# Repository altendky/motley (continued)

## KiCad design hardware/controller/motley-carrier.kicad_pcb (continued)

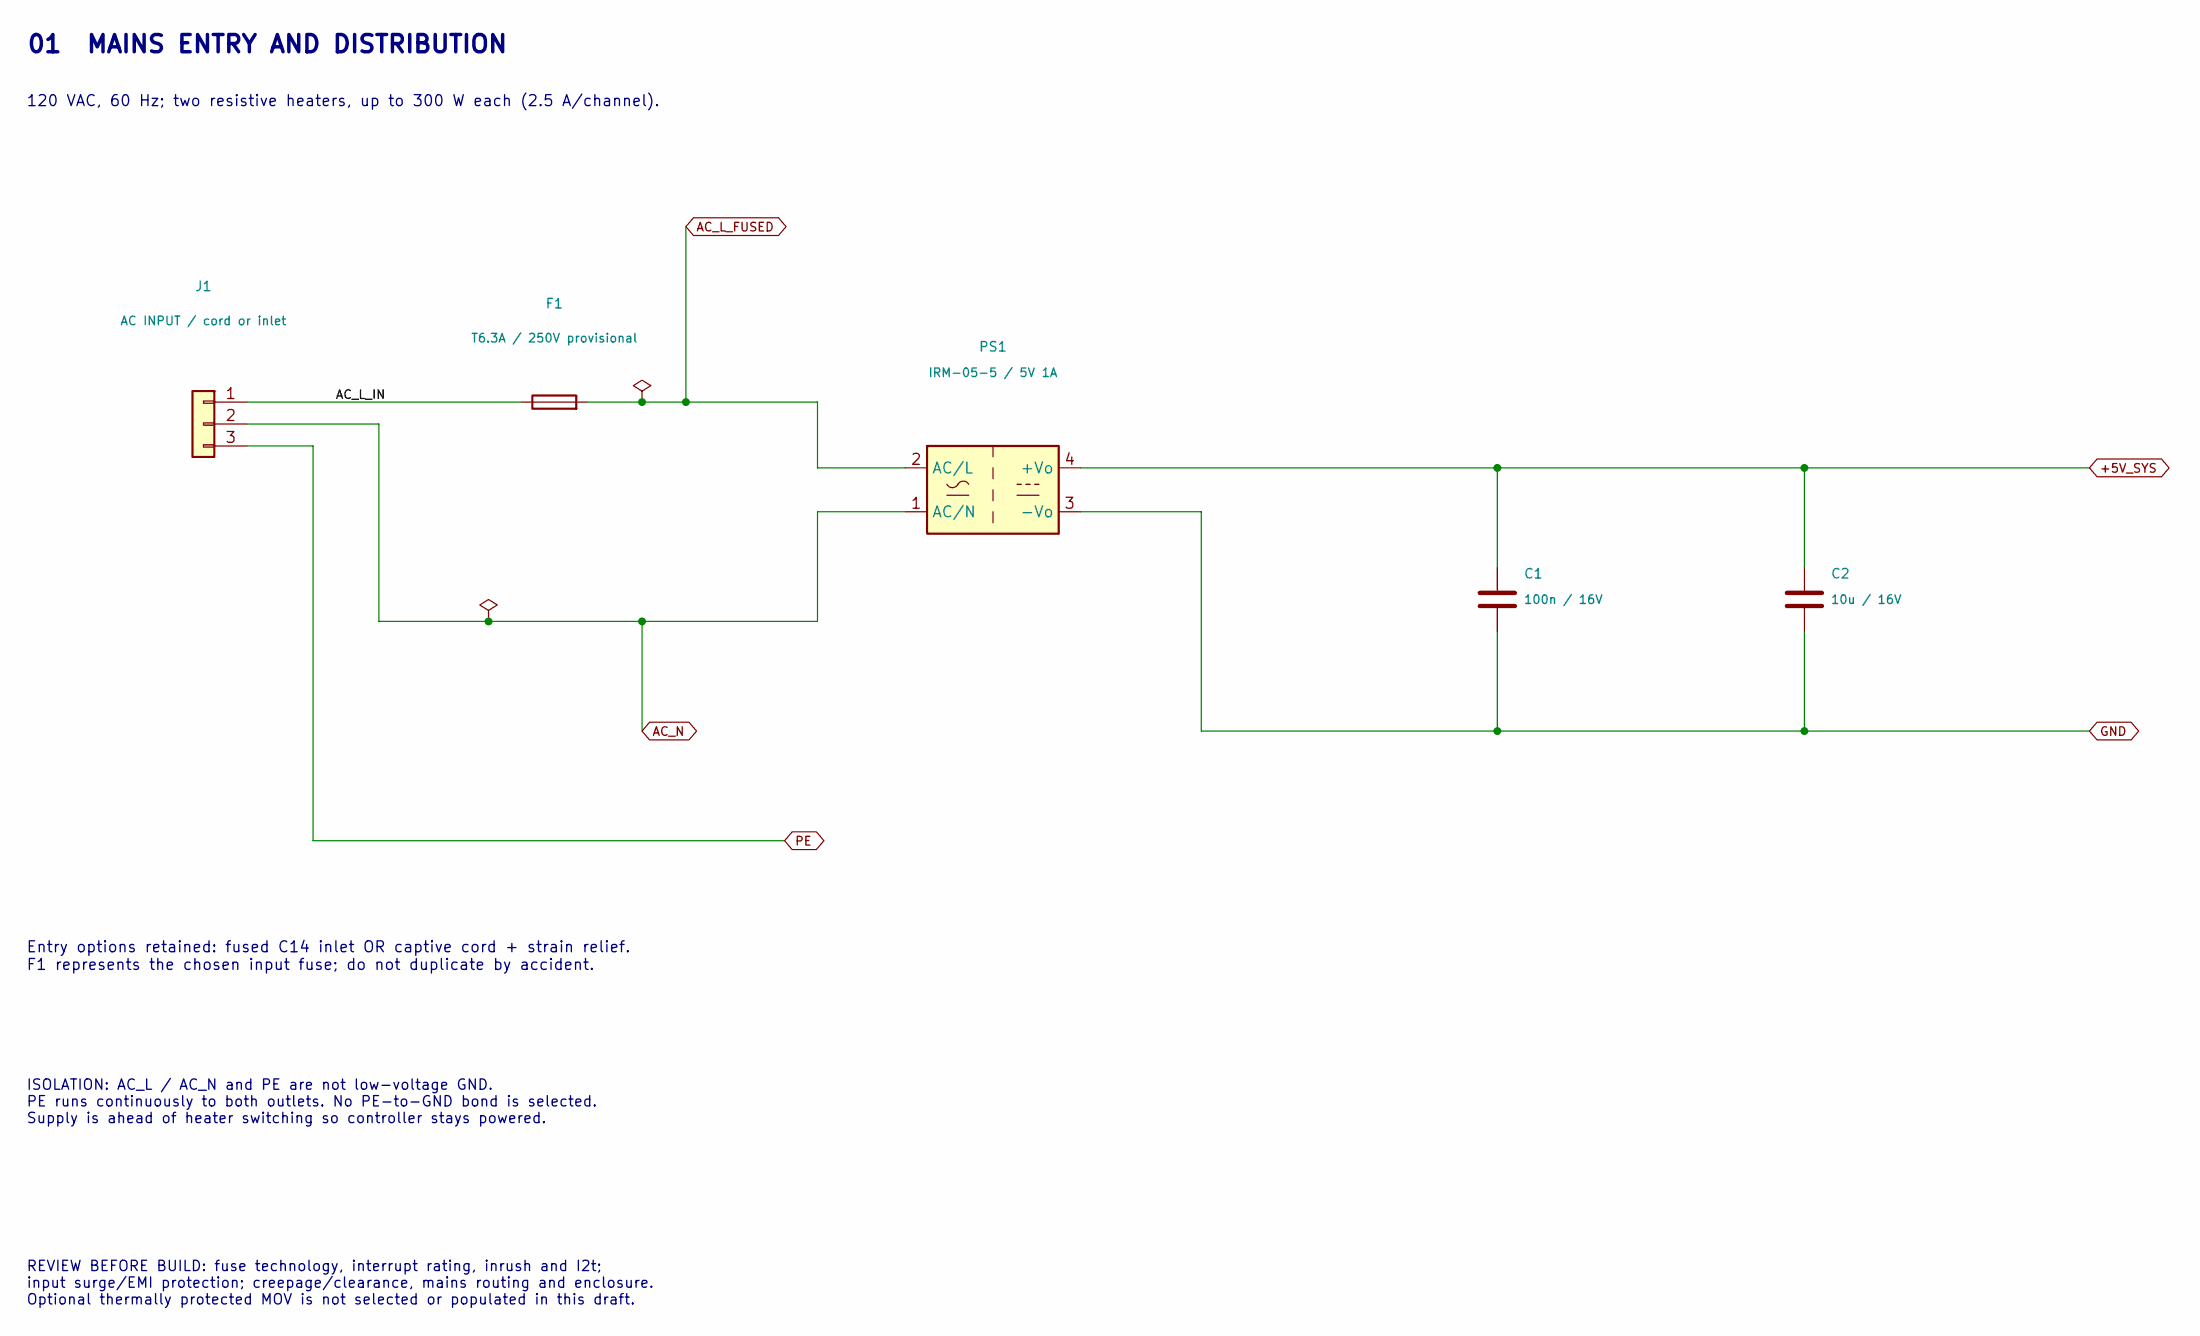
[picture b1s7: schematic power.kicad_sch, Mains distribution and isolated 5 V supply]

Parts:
C1: 100n / 16V; C_0805_2012Metric
C2: 10u / 16V; C_0805_2012Metric
F1: T6.3A / 250V provisional; Fuseholder_Schurter_OGN_0031.8201_P22.50mm_Covered; MPN 0031.8201; LCSC C3204125
J1: AC INPUT / cord or inlet; TerminalBlock_GOOSVN_GS007S_P5.08mm_1x03_Horizontal; MPN GS007S-5.08-03P-11-00A(H); LCSC C5142603
PS1: IRM-05-5 / 5V 1A; Converter_ACDC_MeanWell_IRM-05-xx_THT; LCSC C48603696

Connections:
+5V_SYS: C1.1, C2.1, PS1.4 (+Vo); also elsewhere on the board
/Mains input and isolated 5 V supply/AC_L_IN: F1.1, J1.1
AC_L_FUSED: F1.2, PS1.2 (AC/L); also elsewhere on the board
AC_N: J1.2, PS1.1 (AC/N); also elsewhere on the board
GND: C1.2, C2.2, PS1.3 (-Vo); also elsewhere on the board
PE: J1.3; also elsewhere on the board

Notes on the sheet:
01 MAINS ENTRY AND DISTRIBUTION
120 VAC, 60 Hz; two resistive heaters, up to 300 W each (2.5 A/channel).
ISOLATION: AC_L / AC_N and PE are not low-voltage GND. PE runs continuously to both outlets. No PE-to-GND bond is selected. Supply is ahead of heater switching so controller stays powered.
Entry options retained: fused C14 inlet OR captive cord + strain relief. F1 represents the chosen input fuse; do not duplicate by accident.
REVIEW BEFORE BUILD: fuse technology, interrupt rating, inrush and I2t; input surge/EMI protection; creepage/clearance, mains routing and enclosure. Optional thermally protected MOV is not selected or populated in this draft.

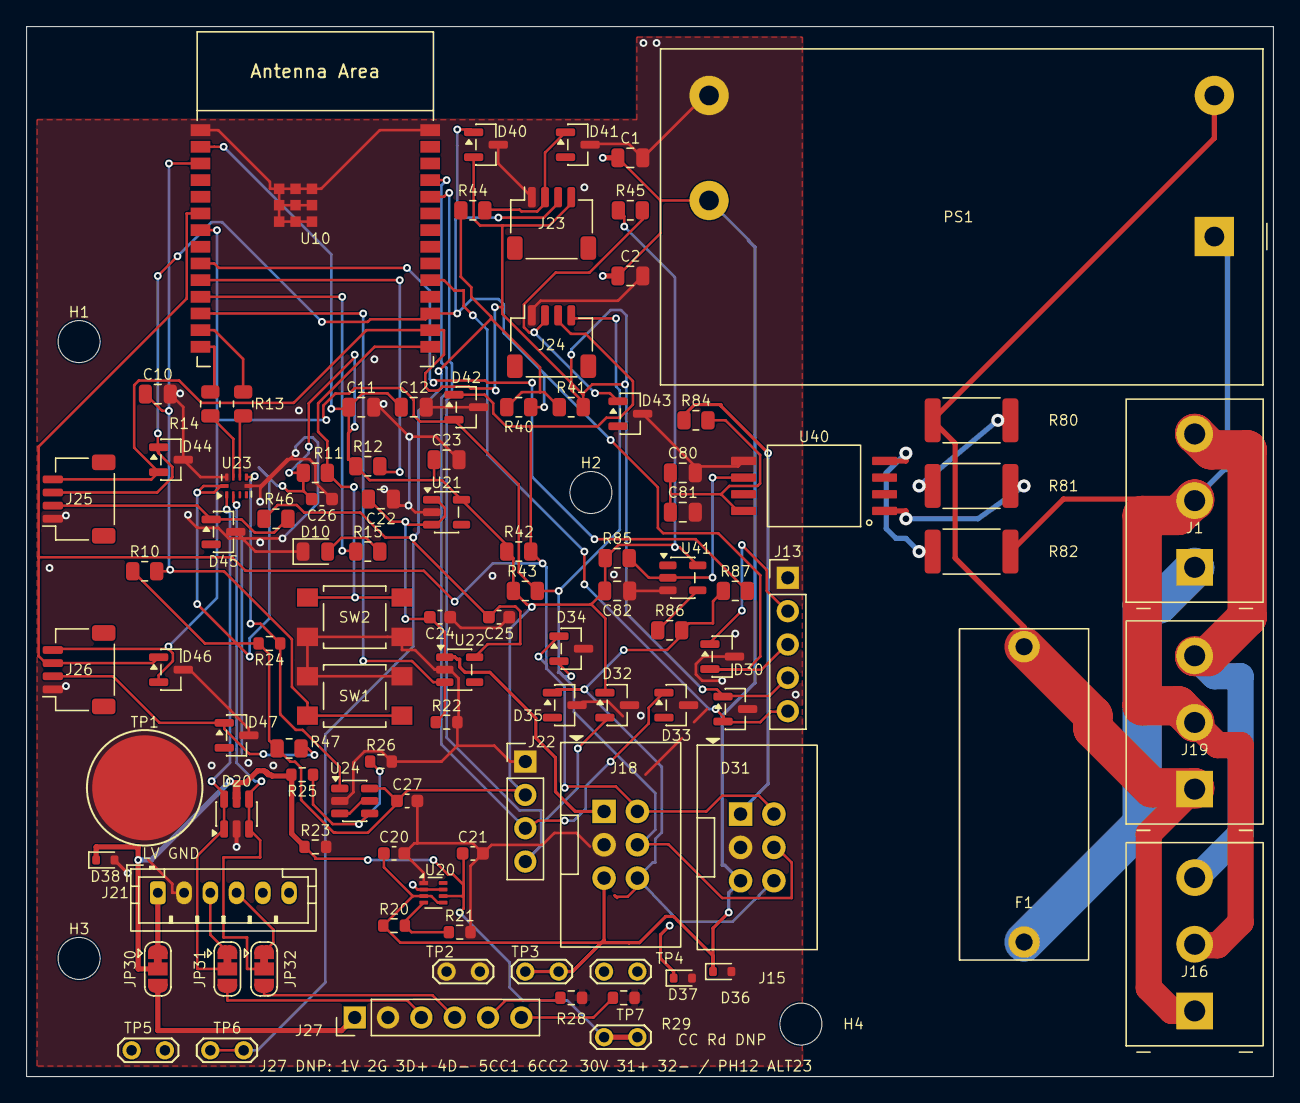
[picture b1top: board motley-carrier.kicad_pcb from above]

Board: 4 copper layers, 95.0 x 80.0 mm, 104 parts (0 on the bottom side), 53 nets.

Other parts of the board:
H1, H2, H3, H4: M3 / PROVISIONAL; MountingHole_3.2mm_M3

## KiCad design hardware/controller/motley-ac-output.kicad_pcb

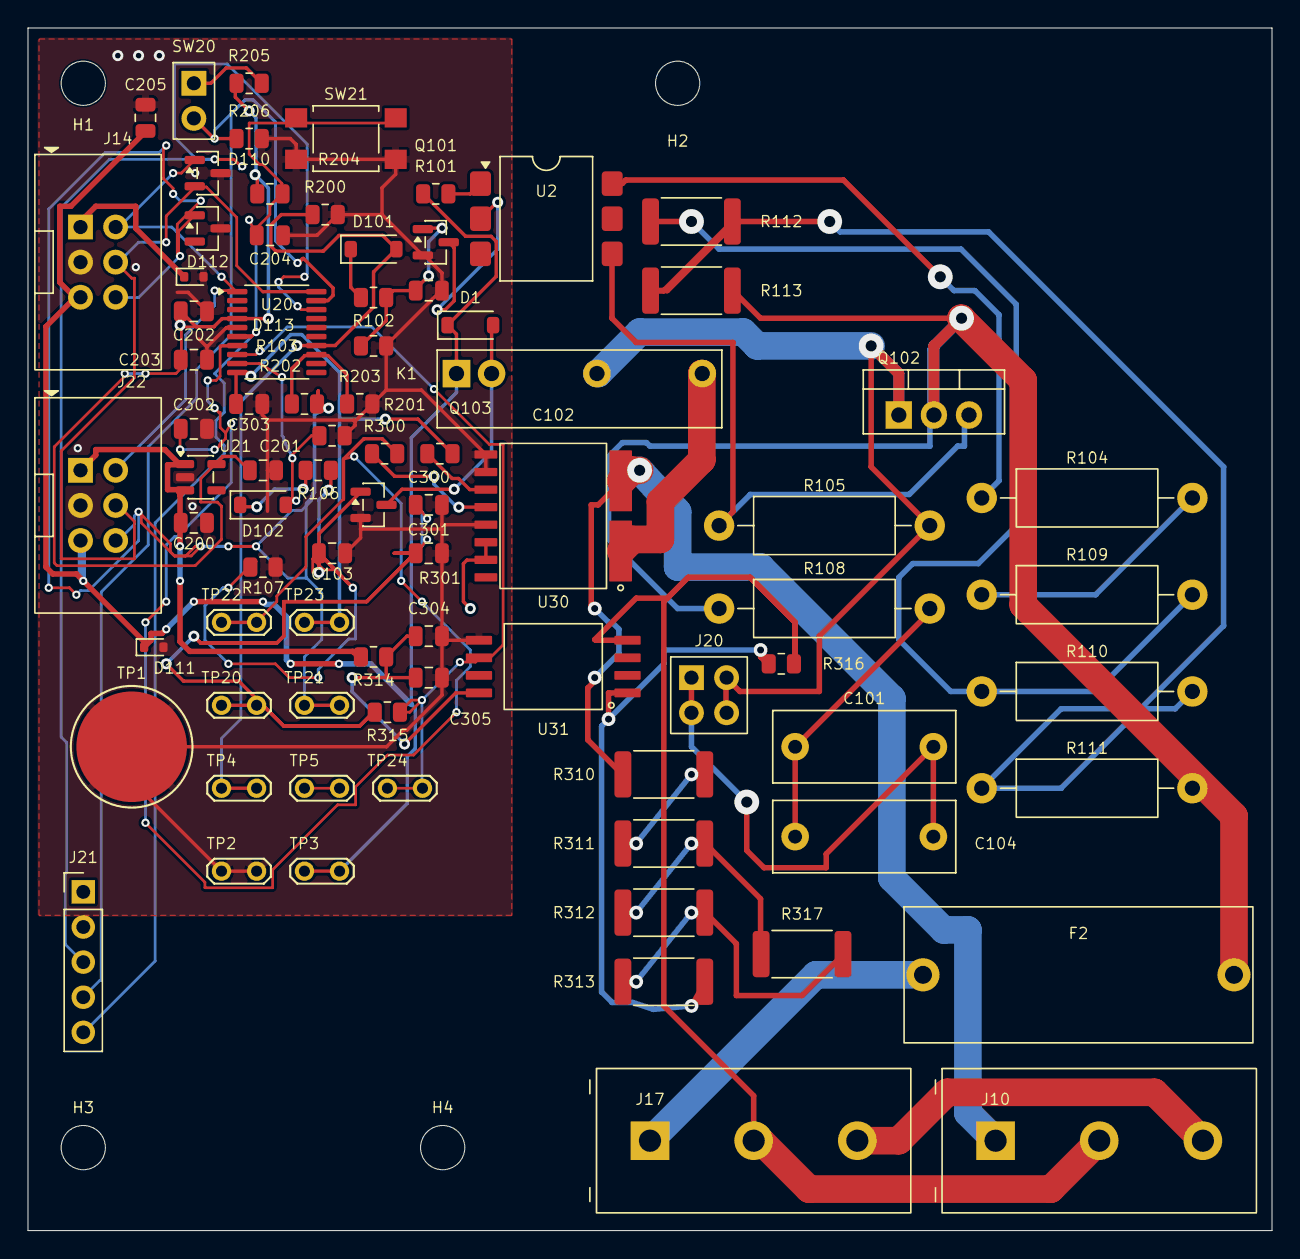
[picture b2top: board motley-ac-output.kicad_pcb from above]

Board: 4 copper layers, 90.0 x 87.0 mm, 85 parts (0 on the bottom side), 45 nets.

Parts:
C101, C104: 4n7 / pulse; C_Rect_L13.0mm_W5.0mm_P10.00mm_FKS3_FKP3_MKS4
C102: 1n / 50V; C_0805_2012Metric
C103: 100n / 50V; C_0805_2012Metric
C200: 1u / 16V; C_0805_2012Metric
C201: 4.7u / 10V; C_0805_2012Metric
C202, C204, C205, C304: 100n / 16V; C_0805_2012Metric
C203, C301: 1u / 10V; C_0805_2012Metric
C300: 100n / 10V; C_0805_2012Metric
C302, C303: 1n / 10V; C_0805_2012Metric
C305: 10n / 16V; C_0805_2012Metric
D1, D101, D102: 1N4148W; D_SOD-123
D110, D112: PESD5V0S2BT,215; SOT-23
D111, D113: ESD5Z6.0T1G; D_SOD-523
F2: T3.15A provisional; Fuseholder_Schurter_OGN_0031.8201_P22.50mm_Covered
H1, H2, H3, H4: M3 / PROVISIONAL; MountingHole_3.2mm_M3
J10: Qualtek 738W-X2/03 (wired); TerminalBlock_GOOSVN_GS007S_P7.50mm_1x03_Horizontal
J14: OUTPUT BUS / IDC6; Kinghelm_KH-2.54PH180-2X3P-L8.9_Vertical
J17: MAINS LINK / provisional terminal; TerminalBlock_GOOSVN_GS007S_P7.50mm_1x03_Horizontal
J20: SNUBBER CONFIG; Samtec_HMTSW-102-07-L-D-200_Vertical
J21: 3V3 SWD / SERVICE; PinHeader_1x05_P2.54mm_Vertical
J22: OUTPUT BUS / DNP; Kinghelm_KH-2.54PH180-2X3P-L8.9_Vertical
K1: G6DN-1A-L DC5; Relay_G6DN_1A_L_DC5_Study
Q101, Q103: MMBT3904; SOT-23
Q102: BTA08-600SWRG; TO-220-3_Vertical
R101: 270; R_0805_2012Metric
R102: 470; R_0805_2012Metric
R103, R107, R204: 10k; R_0805_2012Metric
R104, R109, R110, R111: 1k2 / PR02; Vishay_PR02_P15.24mm
R105, R108: 330 / PR02; Vishay_PR02_P15.24mm
R106: 200 / 1%; R_0805_2012Metric
R112, R113: 0 / LOW bypass; R_2512_6332Metric
R200, R201: 100k / OFF; R_0805_2012Metric
R202: 1k / SYNC; R_0805_2012Metric
R203: 100k / SYNC default; R_0805_2012Metric
R205: 1k / boot bias; R_0805_2012Metric
R206: 47k / RUN; R_0805_2012Metric
R300, R301: 100; R_0805_2012Metric
R310, R311, R312, R317: 8k2; R_2512_6332Metric
R313: 0 / LOW link; R_2512_6332Metric
R314: 240; R_0805_2012Metric
R315: 4k7; R_0805_2012Metric
R316: 2k7; R_0805_2012Metric
SW20: RUN open / RECOVERY closed; Samtec_HMTSW-102-07-G-S-200_Vertical
SW21: RESET; SW_SPST_TL3305A
TP1: TOUCH LV GND; TouchGround_8mm
TP2: GND / LOOP; WireLoop_P2.54
TP3: +5V_SYS / LOOP; WireLoop_P2.54
TP4: HEAT_EN / LOOP; WireLoop_P2.54
TP5: CUT_EN / LOOP; WireLoop_P2.54
TP20: +3V3_OUT; WireLoop_P2.54
TP21: LINE_SYNC; WireLoop_P2.54
TP22: CURRENT_V; WireLoop_P2.54
TP23: CURRENT_REF; WireLoop_P2.54
TP24: OUT_VOLT_N; WireLoop_P2.54
U2: VO3053-X007T / RANDOM PHASE; VO3053_Option7_Study
U20: STM32C011F6P6 / C5456198; TSSOP-20_4.4x6.5mm_P0.65mm
U21: AP2112K-3.3TRG1 / LOGIC; SOT-23-5
U30: TMCS1123B5AQDVGR; TMCS1123_DVG10_Study
U31: ACPL-K370-500E; ACPL_K37x_SSO8_Study

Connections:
+3V3_OUT: C201.1, C202.1, C203.1, C300.1, C301.1, J21.1, R204.1, R205.1, R315.1, TP20.1, U20.4, U21.5, U30.8, U30.9
+5V_LOGIC: C200.1, D113.1, J14.1, J22.1, R314.1, U21.1, U21.3
+5V_SYS: C205.1, D1.1 (K), D111.1, J14.5, J22.5, K1.1 (COIL), R101.1, TP3.1
/Heater 1/TRIAC_A1: J20.2, J20.4, K1.5 (NO), Q102.1 (A1), R105.2
/Local output MCU, power and recovery/OUT_BOOT0_SWCLK: J21.4, R206.1, SW20.2, U20.19
/Local output MCU, power and recovery/OUT_NRST: C204.1, J21.5, R204.2, SW21.1, U20.6
/Local output MCU, power and recovery/OUT_SWDIO: J21.3, U20.18
/Local output MCU, power and recovery/SYNC_IN: R202.1, R203.1, U20.13
AC_L_FUSED: F2.1, J17.1
AC_N: J10.2, J17.2, R316.2, U31.4
CURRENT_REF: C303.1, R301.2, TP23.1, U20.10
CURRENT_V: C302.1, R300.2, TP22.1, U20.7
CUT_EN: D102.2, R201.1, TP5.1, U20.9
CUT_L_UNSENSED: K1.8 (COM), U30.1
GND: C102.2, C103.2, C200.2, C201.2, C202.2, C203.2, C204.2, C205.2, C300.2, C301.2, C302.2, C303.2, C304.2, C305.2, D110.3, D111.2, D112.3, D113.2, J14.3, J21.2, J22.3, Q101.2 (E), Q103.2 (E), R103.2, R107.2, R200.2, R201.2, R203.2, R206.2, SW21.2, TP1.1, TP2.1, U20.5, U21.2, U30.3, U30.4, U30.7, U31.5
HEAT_EN: D101.2, R200.1, TP4.1, U20.14
LINE_SYNC: D112.1, J14.6, J22.6, R202.2, TP21.1
unnamed: C101.1, C104.1, R108.2
unnamed: D1.2 (A), K1.2 (COIL), Q103.3 (C)
unnamed: D101.1, R102.1
unnamed: D102.1, R106.1
unnamed: C101.2, C104.2, J20.1, J20.3
unnamed: C102.1, Q101.1 (B), R102.2, R103.1
unnamed: Q101.3 (C), U2.2
unnamed: F2.2, Q102.2 (A2), R108.1, R111.2, R113.2
unnamed: Q102.3 (G), R105.1, U2.4
unnamed: C103.1, Q103.1 (B), R106.2, R107.1
unnamed: R101.2, U2.1
unnamed: R104.1, U2.6
unnamed: R104.2, R109.1
unnamed: R109.2, R110.1, R112.1
unnamed: R110.2, R111.1, R112.2, R113.1
unnamed: R310.2, R311.1
unnamed: R311.2, R312.1, R317.1
unnamed: R312.2, R313.1, R317.2
unnamed: R205.2, SW20.1
unnamed: R300.1, U30.6
unnamed: R301.1, U30.5
unnamed: R313.2, R316.1, U31.1
unnamed: C304.1, C305.1, R314.2, U31.8
OUTLET_L: J10.1, R310.1, U30.2
OUT_SCL: D110.2, J14.4, J22.4, U20.20
OUT_SDA: D110.1, J14.2, J22.2, U20.1
OUT_VOLT_N: R315.2, TP24.1, U20.8, U31.6
PE: J10.3, J17.3

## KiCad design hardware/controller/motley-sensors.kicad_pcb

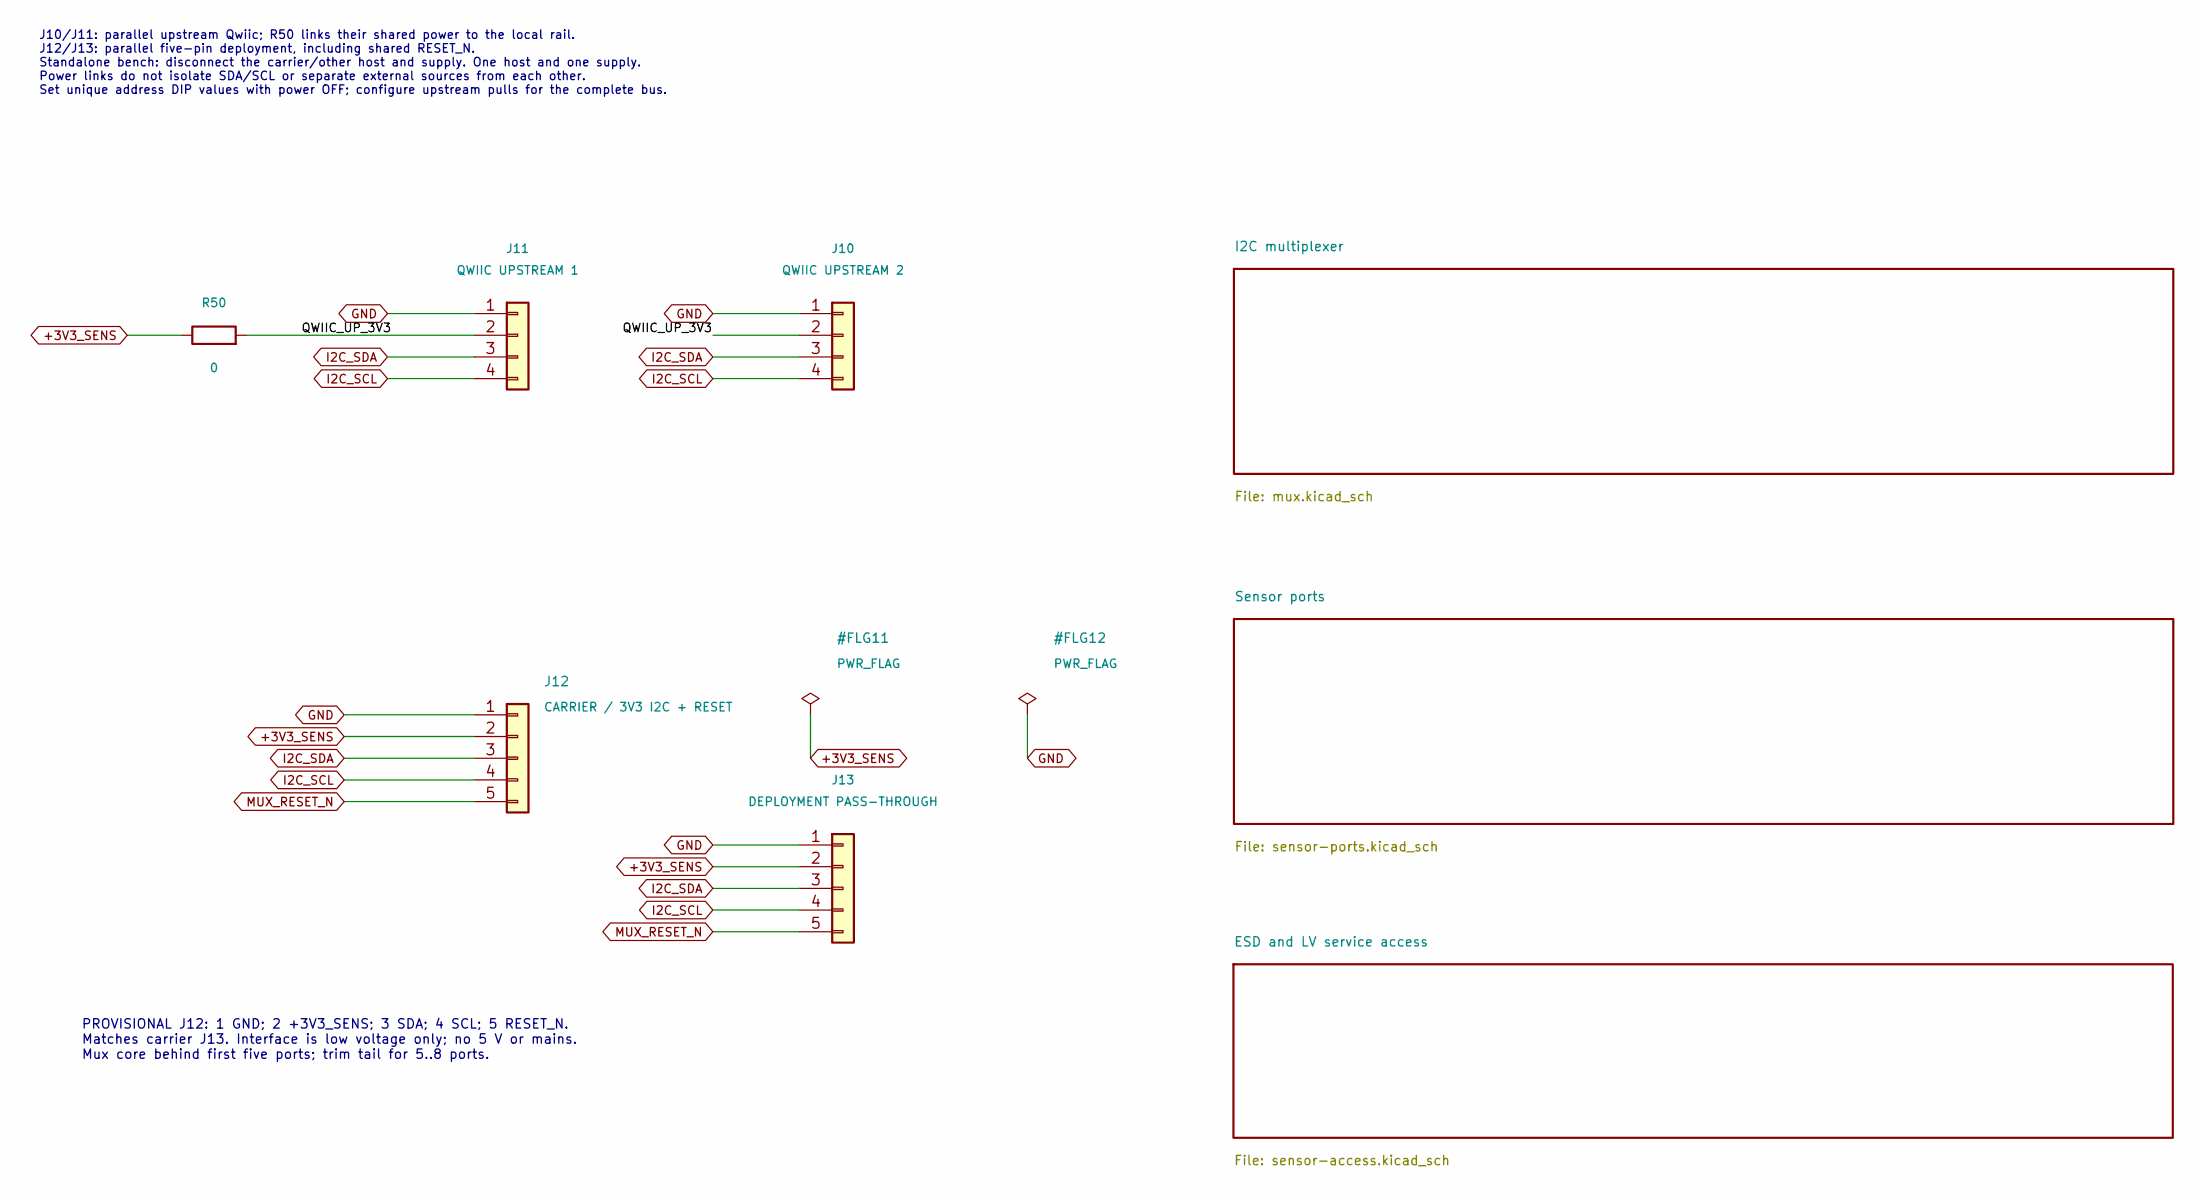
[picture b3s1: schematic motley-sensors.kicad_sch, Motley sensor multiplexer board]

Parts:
J10: QWIIC UPSTREAM 2; JST_SH_SM04B-SRSS-TB_1x04-1MP_P1.00mm_Horizontal
J11: QWIIC UPSTREAM 1; JST_SH_SM04B-SRSS-TB_1x04-1MP_P1.00mm_Horizontal
J12: CARRIER / 3V3 I2C + RESET; PinHeader_1x05_P2.54mm_Vertical
J13: DEPLOYMENT PASS-THROUGH; PinHeader_1x05_P2.54mm_Vertical
R50: 0; R_0805_2012Metric

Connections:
+3V3_SENS: J12.2, J13.2, R50.1; also elsewhere on the board
/QWIIC_UP_3V3: J10.2, J11.2, R50.2
GND: J10.1, J11.1, J12.1, J13.1; also elsewhere on the board
I2C_SCL: J10.4, J11.4, J12.4, J13.4; also elsewhere on the board
I2C_SDA: J10.3, J11.3, J12.3, J13.3; also elsewhere on the board
MUX_RESET_N: J12.5, J13.5; also elsewhere on the board

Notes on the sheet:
PROVISIONAL J12: 1 GND; 2 +3V3_SENS; 3 SDA; 4 SCL; 5 RESET_N. Matches carrier J13. Interface is low voltage only; no 5 V or mains. Mux core behind first five ports; trim tail for 5..8 ports.
J10/J11: parallel upstream Qwiic; R50 links their shared power to the local rail. J12/J13: parallel five-pin deployment, including shared RESET_N. Standalone bench: disconnect the carrier/other host and supply. One host and one supply. Power links do not isolate SDA/SCL or separate external sources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

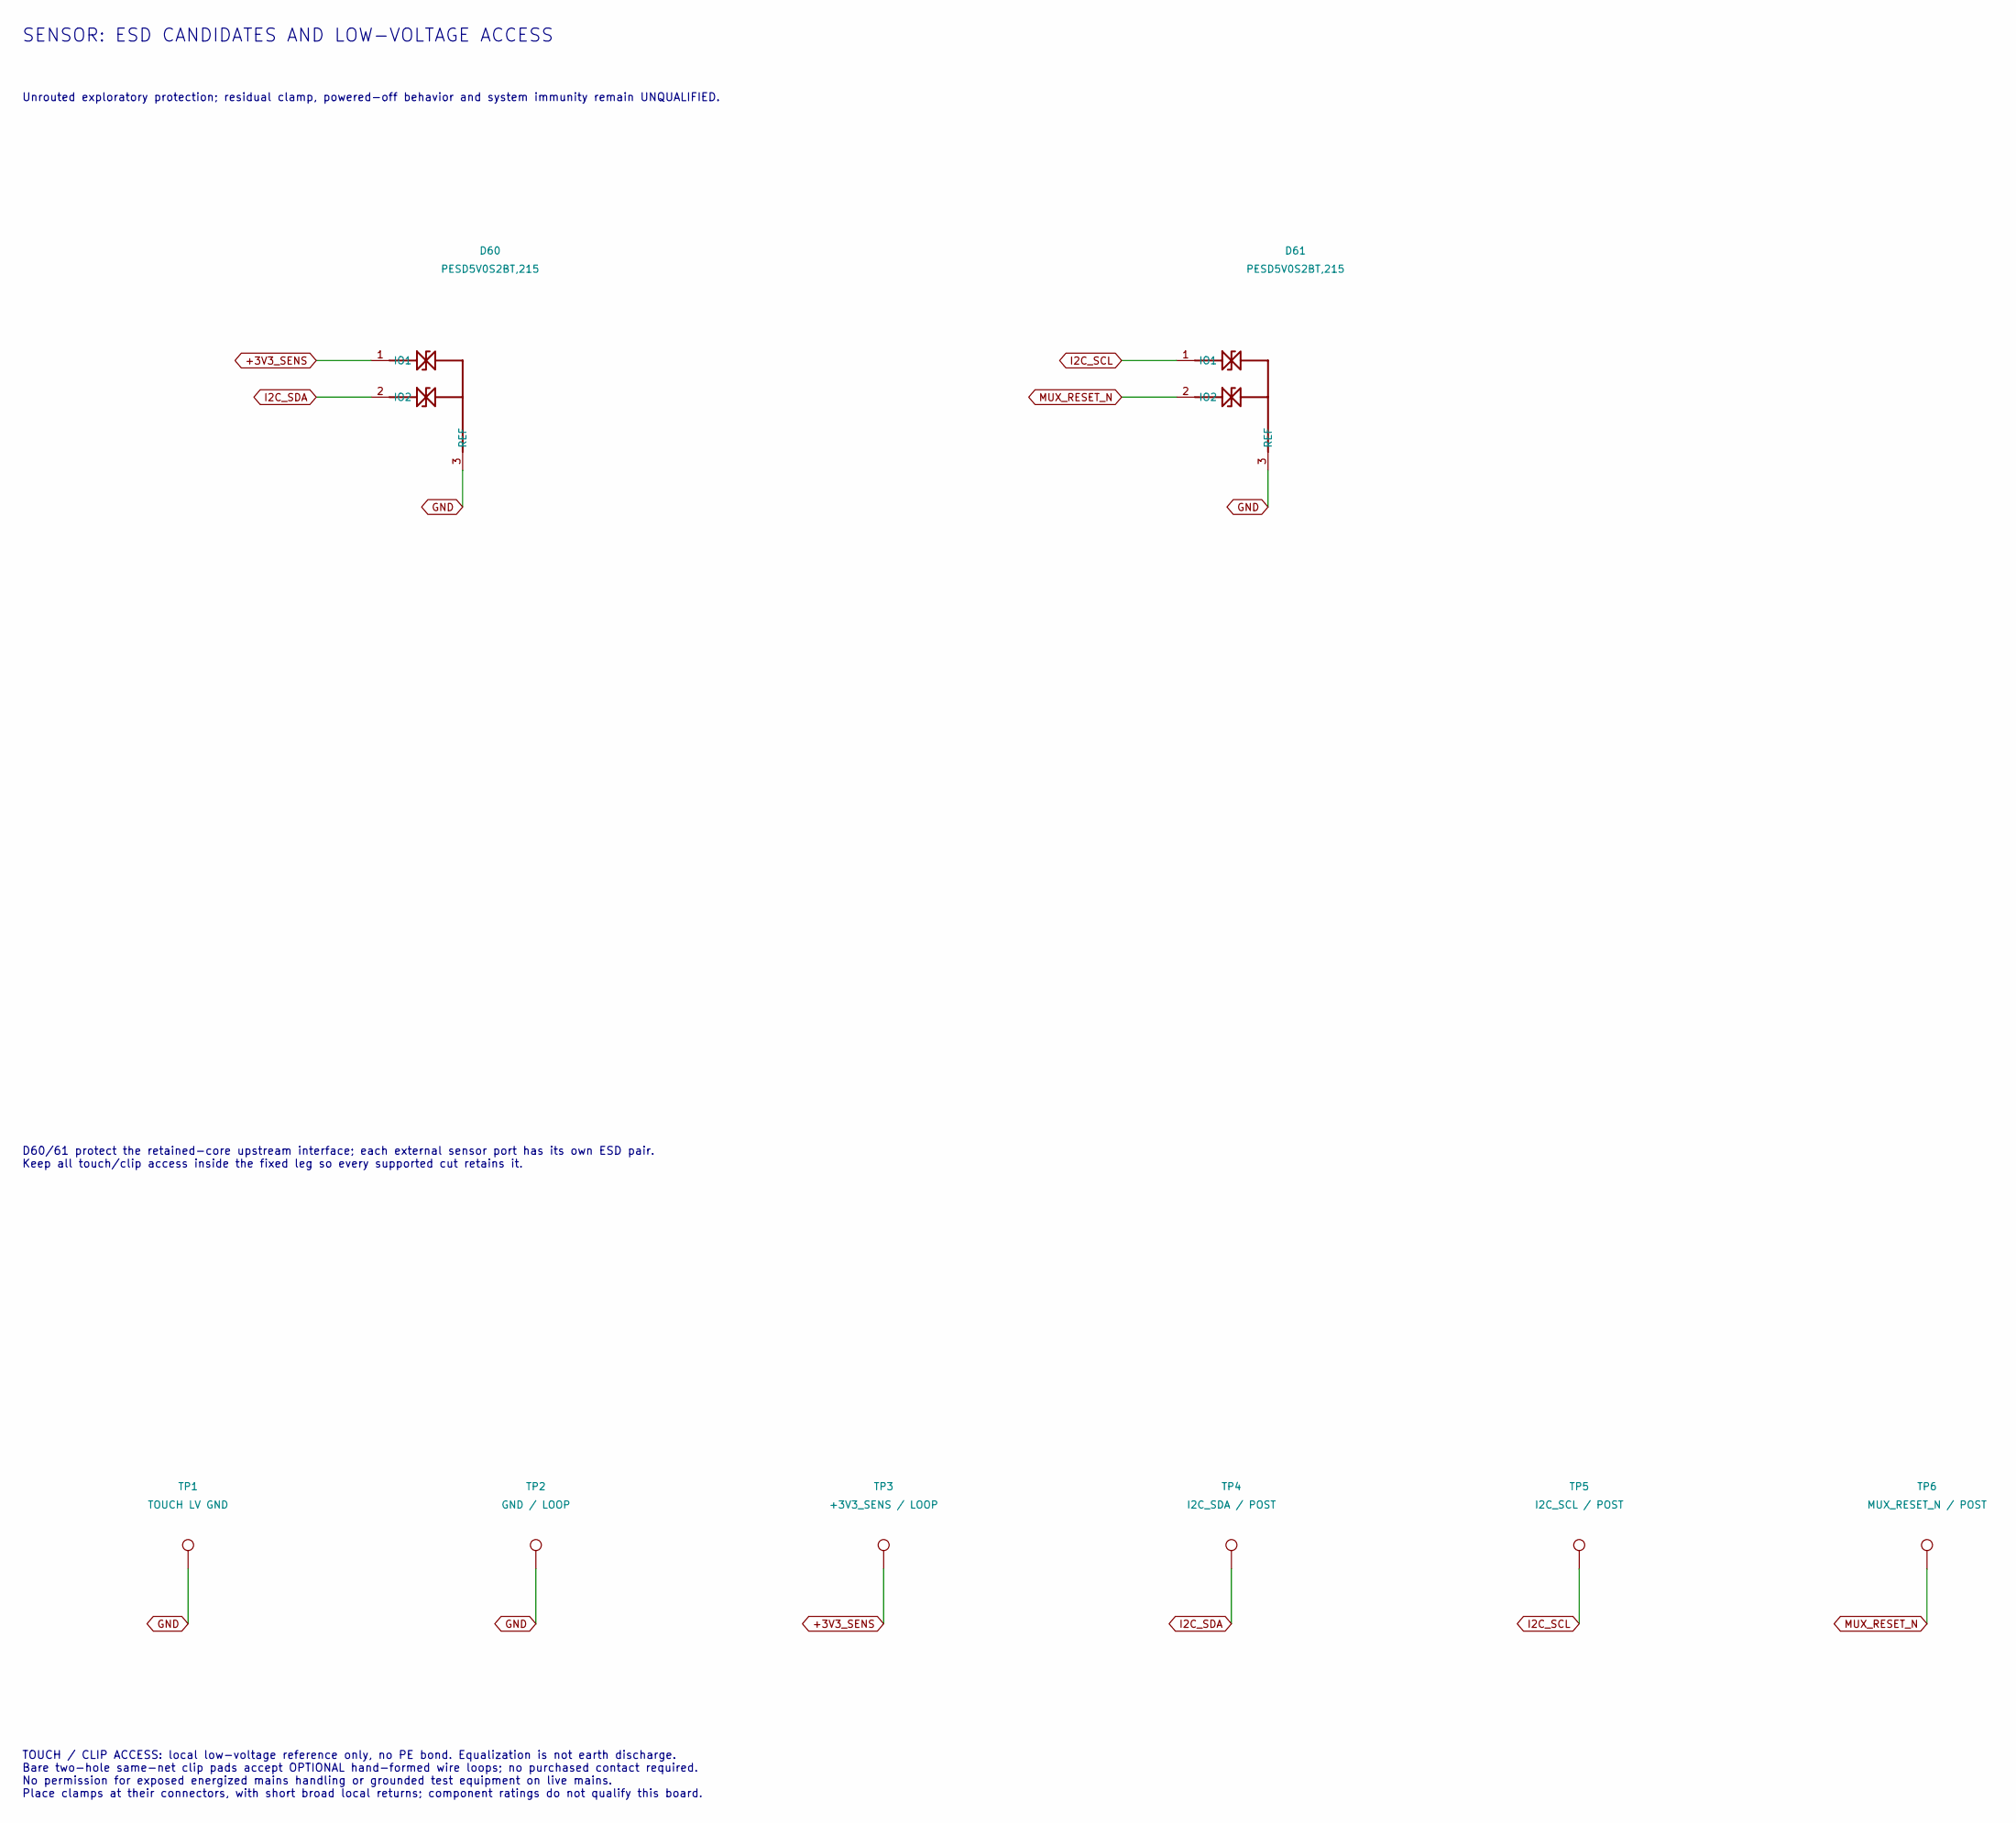
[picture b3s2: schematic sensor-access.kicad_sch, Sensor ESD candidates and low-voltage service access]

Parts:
D60, D61: PESD5V0S2BT,215; SOT-23
TP1: TOUCH LV GND; TouchGround_8mm
TP2: GND / LOOP; WireLoop_P2.54
TP3: +3V3_SENS / LOOP; WireLoop_P2.54
TP4: I2C_SDA / POST; WirePost_1mm
TP5: I2C_SCL / POST; WirePost_1mm
TP6: MUX_RESET_N / POST; WirePost_1mm

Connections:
+3V3_SENS: D60.1 (IO1), TP3.1; also elsewhere on the board
GND: D60.3 (REF), D61.3 (REF), TP1.1, TP2.1; also elsewhere on the board
I2C_SCL: D61.1 (IO1), TP5.1; also elsewhere on the board
I2C_SDA: D60.2 (IO2), TP4.1; also elsewhere on the board
MUX_RESET_N: D61.2 (IO2), TP6.1; also elsewhere on the board

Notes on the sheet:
D60/61 protect the retained-core upstream interface; each external sensor port has its own ESD pair. Keep all touch/clip access inside the fixed leg so every supported cut retains it.
SENSOR: ESD CANDIDATES AND LOW-VOLTAGE ACCESS
Unrouted exploratory protection; residual clamp, powered-off behavior and system immunity remain UNQUALIFIED.
TOUCH / CLIP ACCESS: local low-voltage reference only, no PE bond. Equalization is not earth discharge. Bare two-hole same-net clip pads accept OPTIONAL hand-formed wire loops; no purchased contact required. No permission for exposed energized mains handling or grounded test equipment on live mains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

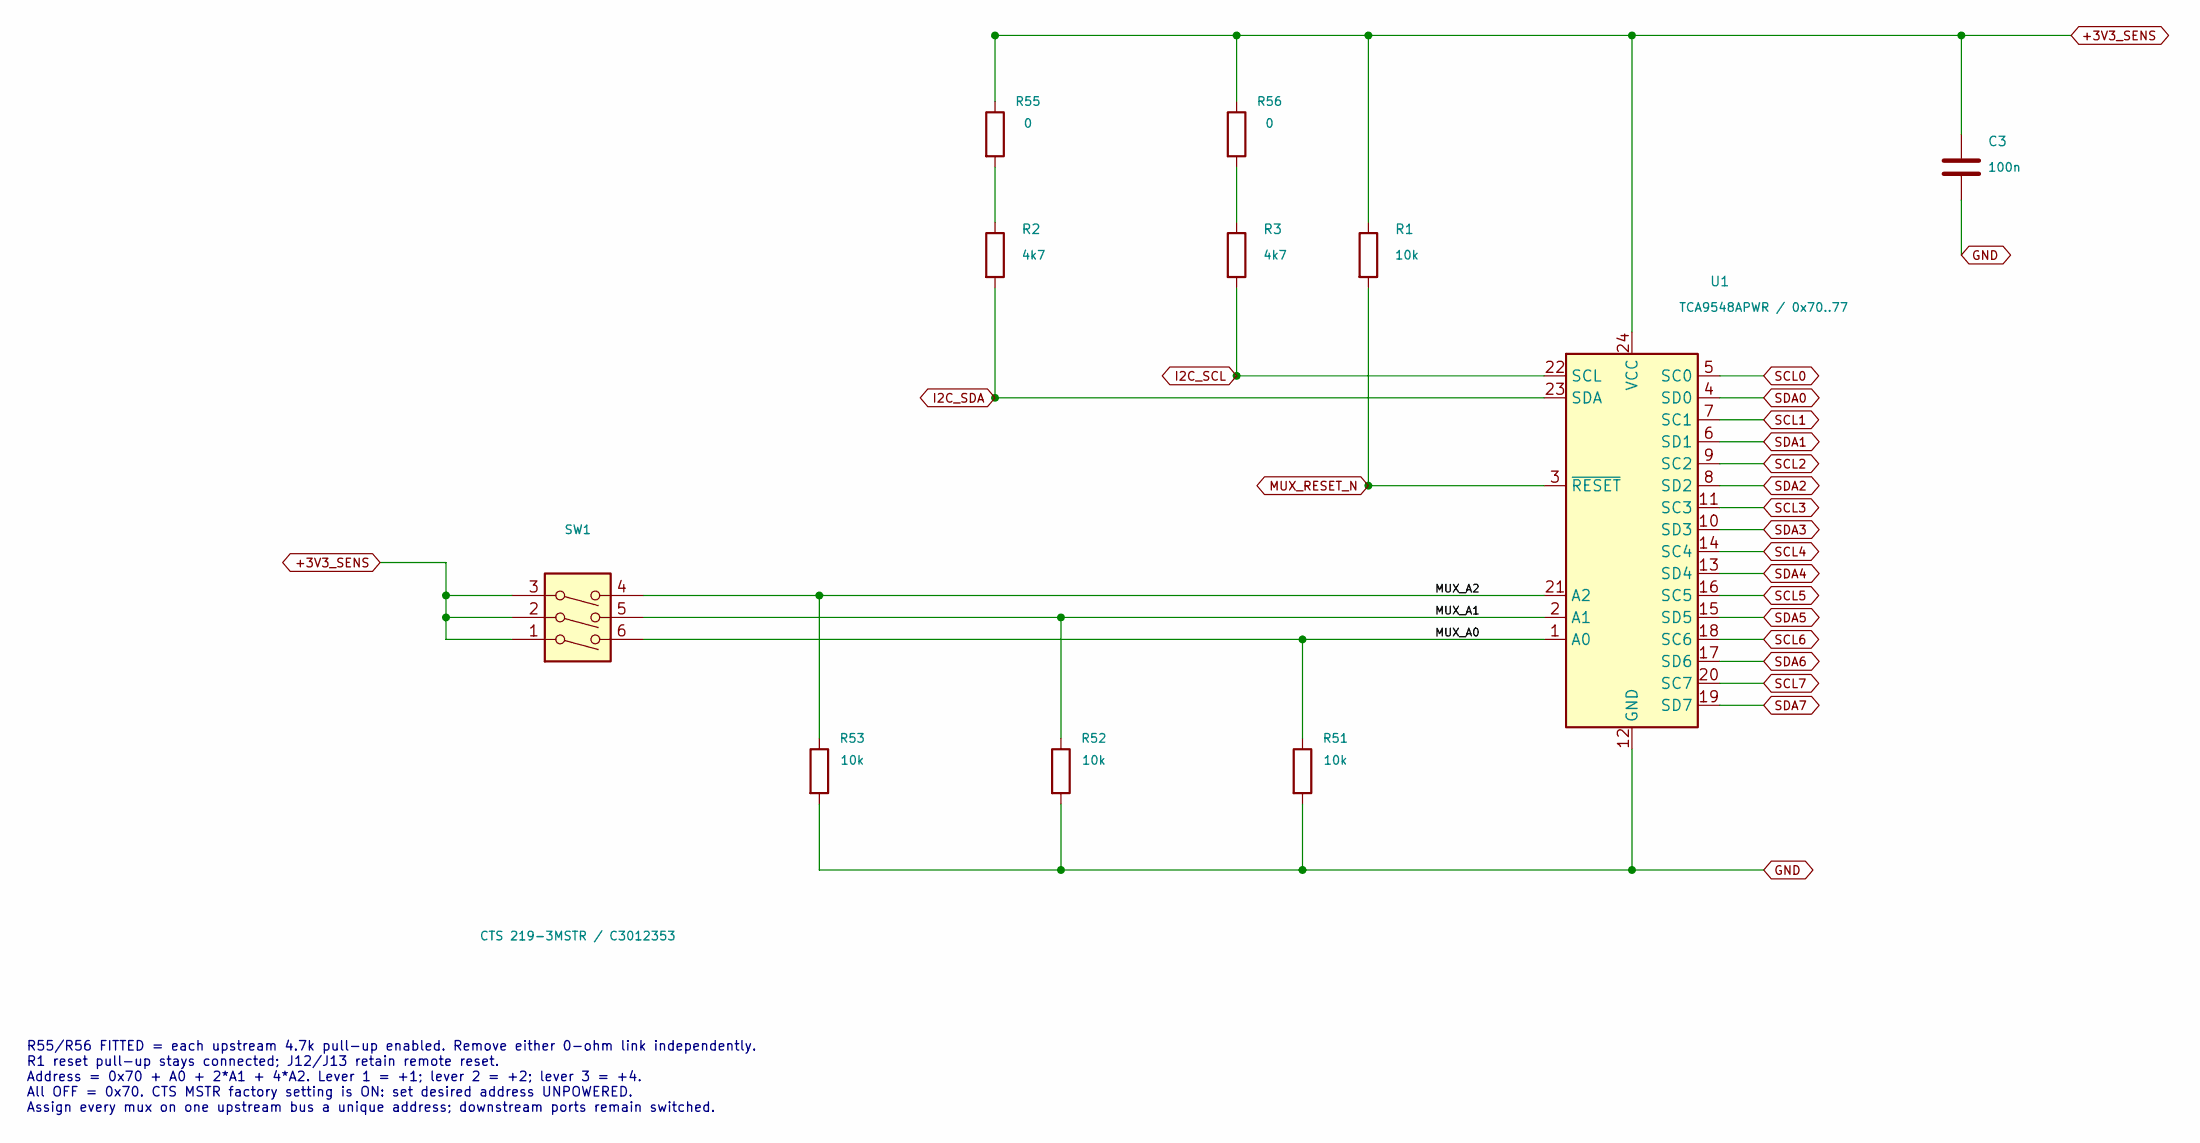
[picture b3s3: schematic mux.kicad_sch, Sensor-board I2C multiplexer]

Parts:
C3: 100n; C_0805_2012Metric
R1, R51, R52, R53: 10k; R_0805_2012Metric
R2, R3: 4k7; R_0805_2012Metric
R55, R56: 0; R_0805_2012Metric
SW1: CTS 219-3MSTR / C3012353; SW_DIP_SPSTx03_Slide_6.7x9.18mm_W8.61mm_P2.54mm_LowProfile
U1: TCA9548APWR / 0x70..77; TSSOP-24_4.4x7.8mm_P0.65mm

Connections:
+3V3_SENS: C3.1, R1.1, R55.1, R56.1, SW1.1, SW1.2, SW1.3, U1.24 (VCC); also elsewhere on the board
/I2C multiplexer/MUX_A0: R51.1, SW1.6, U1.1 (A0)
/I2C multiplexer/MUX_A1: R52.1, SW1.5, U1.2 (A1)
/I2C multiplexer/MUX_A2: R53.1, SW1.4, U1.21 (A2)
GND: C3.2, R51.2, R52.2, R53.2, U1.12 (GND); also elsewhere on the board
I2C_SCL: R3.2, U1.22 (SCL); also elsewhere on the board
I2C_SDA: R2.2, U1.23 (SDA); also elsewhere on the board
MUX_RESET_N: R1.2, U1.3 (~RESET); also elsewhere on the board
unnamed: R2.1, R55.2
unnamed: R3.1, R56.2
SCL0: U1.5 (SC0); also elsewhere on the board
SCL1: U1.7 (SC1); also elsewhere on the board
SCL2: U1.9 (SC2); also elsewhere on the board
SCL3: U1.11 (SC3); also elsewhere on the board
SCL4: U1.14 (SC4); also elsewhere on the board
SCL5: U1.16 (SC5); also elsewhere on the board
SCL6: U1.18 (SC6); also elsewhere on the board
SCL7: U1.20 (SC7); also elsewhere on the board
SDA0: U1.4 (SD0); also elsewhere on the board
SDA1: U1.6 (SD1); also elsewhere on the board
SDA2: U1.8 (SD2); also elsewhere on the board
SDA3: U1.10 (SD3); also elsewhere on the board
SDA4: U1.13 (SD4); also elsewhere on the board
SDA5: U1.15 (SD5); also elsewhere on the board
SDA6: U1.17 (SD6); also elsewhere on the board
SDA7: U1.19 (SD7); also elsewhere on the board

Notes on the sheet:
R55/R56 FITTED = each upstream 4.7k pull-up enabled. Remove either 0-ohm link independently. R1 reset pull-up stays connected; J12/J13 retain remote reset. Address = 0x70 + A0 + 2*A1 + 4*A2. Lever 1 = +1; lever 2 = +2; lever 3 = +4. All OFF = 0x70. CTS MSTR factory setting is ON: set desired addres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

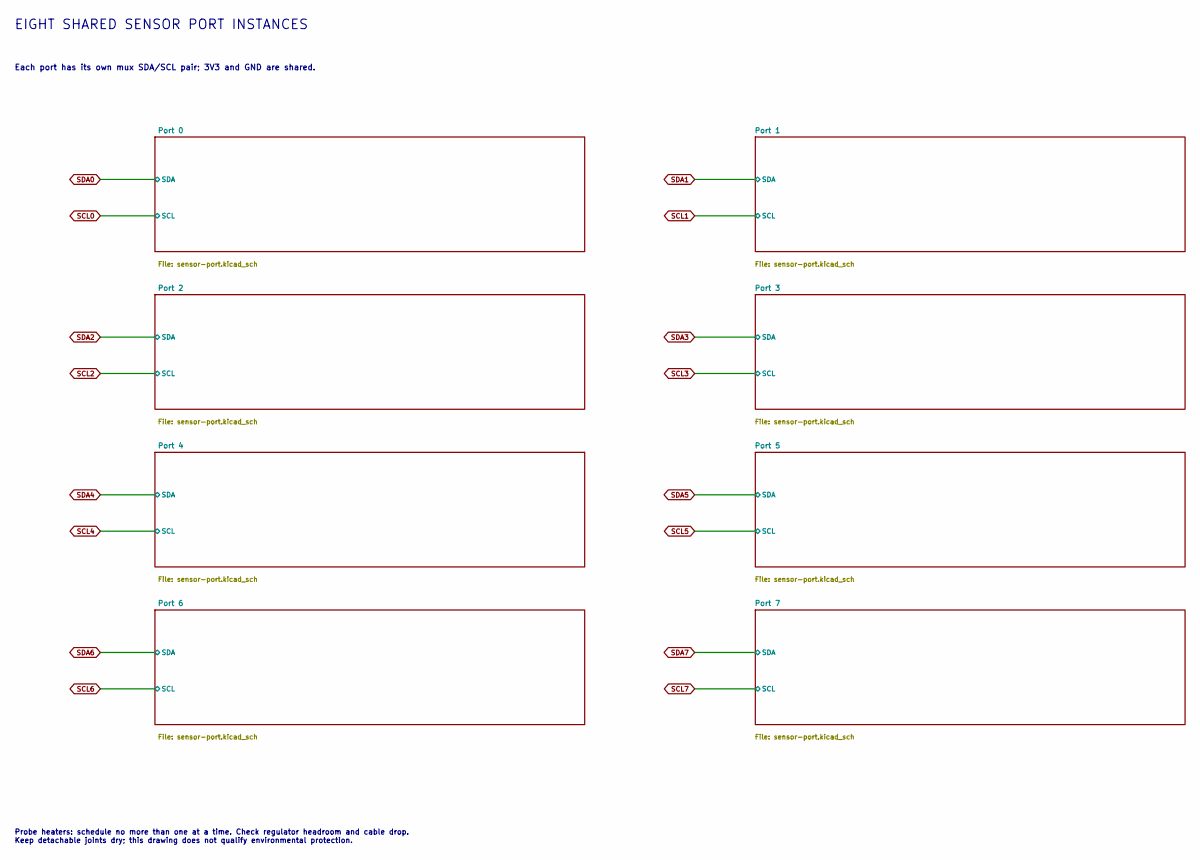
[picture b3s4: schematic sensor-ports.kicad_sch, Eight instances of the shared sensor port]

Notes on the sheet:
Each port has its own mux SDA/SCL pair; 3V3 and GND are shared.
Probe heaters: schedule no more than one at a time. Check regulator headroom and cable drop. Keep detachable joints dry; this drawing does not qualify environmental protection.
EIGHT SHARED SENSOR PORT INSTANCES
